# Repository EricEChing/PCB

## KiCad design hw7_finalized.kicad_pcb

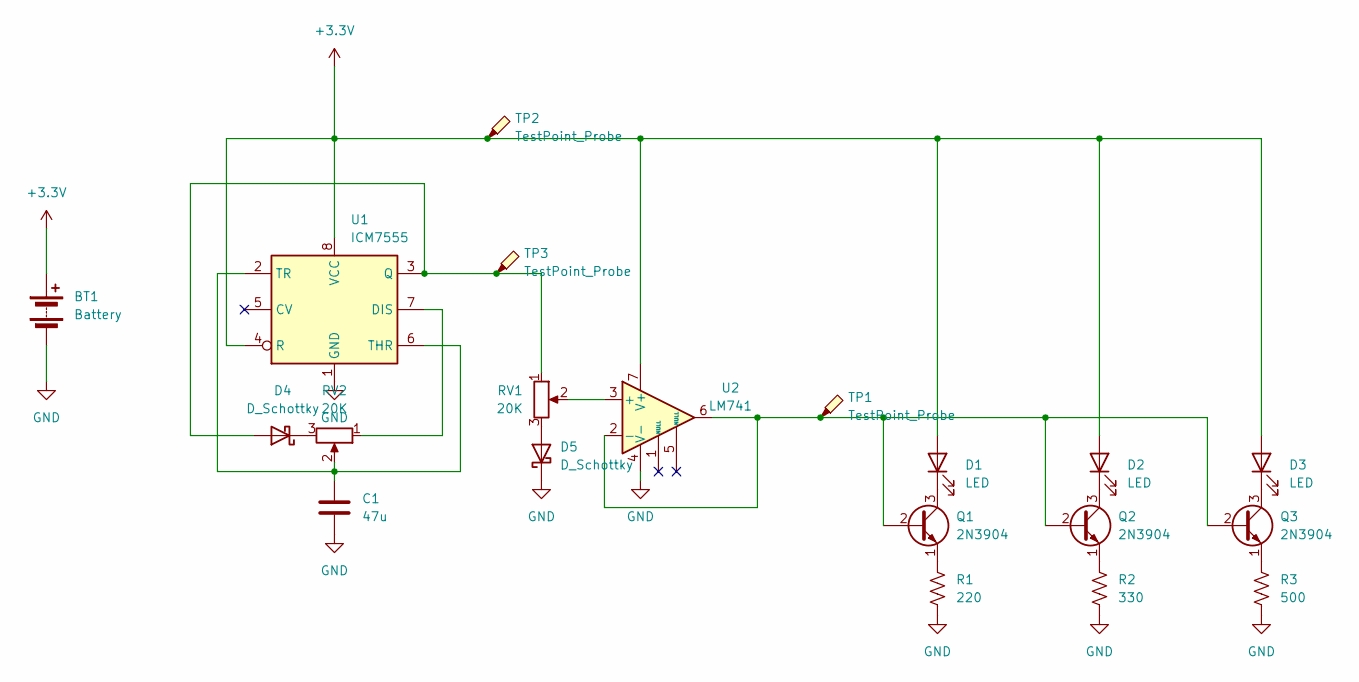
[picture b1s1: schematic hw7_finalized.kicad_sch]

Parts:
BT1: Battery; BAT_1026
C1: 47u; CP_Radial_D5.0mm_P2.00mm
D1, D2, D3: LED; LED_D3.0mm
D4, D5: D_Schottky; D_5KPW_P7.62mm_Vertical_AnodeUp
Q1, Q2, Q3: 2N3904; TO-92_Inline
R1: 220; R_Axial_DIN0207_L6.3mm_D2.5mm_P2.54mm_Vertical
R2: 330; R_Axial_DIN0207_L6.3mm_D2.5mm_P2.54mm_Vertical
R3: 500; R_Axial_DIN0207_L6.3mm_D2.5mm_P2.54mm_Vertical
RV1, RV2: 20K; Potentiometer_ACP_CA6-H2,5_Horizontal
TP1, TP2, TP3: TestPoint_Probe; TestPoint_Pad_D4.0mm
U1: ICM7555; DIP-8_W7.62mm
U2: LM741; DIP-8_W7.62mm

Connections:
+3.3V: BT1.P (+), D1.2 (A), D2.2 (A), D3.2 (A), TP2.1, U1.4 (R), U1.8 (VCC), U2.7 (V+)
GND: BT1.N (-), C1.2, D5.1 (K), R1.2, R2.2, R3.2, U1.1 (GND), U2.4 (V-)
unnamed: D1.1 (K), Q1.3 (C)
unnamed: D2.1 (K), Q2.3 (C)
unnamed: D3.1 (K), Q3.3 (C)
unnamed: D4.2 (A), RV1.1, TP3.1, U1.3 (Q)
unnamed: D4.1 (K), RV2.3
unnamed: D5.2 (A), RV1.3
unnamed: Q1.2 (B), Q2.2 (B), Q3.2 (B), TP1.1, U2.2 (-), U2.6
unnamed: Q1.1 (E), R1.1
unnamed: Q2.1 (E), R2.1
unnamed: Q3.1 (E), R3.1
unnamed: RV2.1, U1.7 (DIS)
unnamed: C1.1, RV2.2, U1.2 (TR), U1.6 (THR)
unnamed: RV1.2, U2.3 (+)

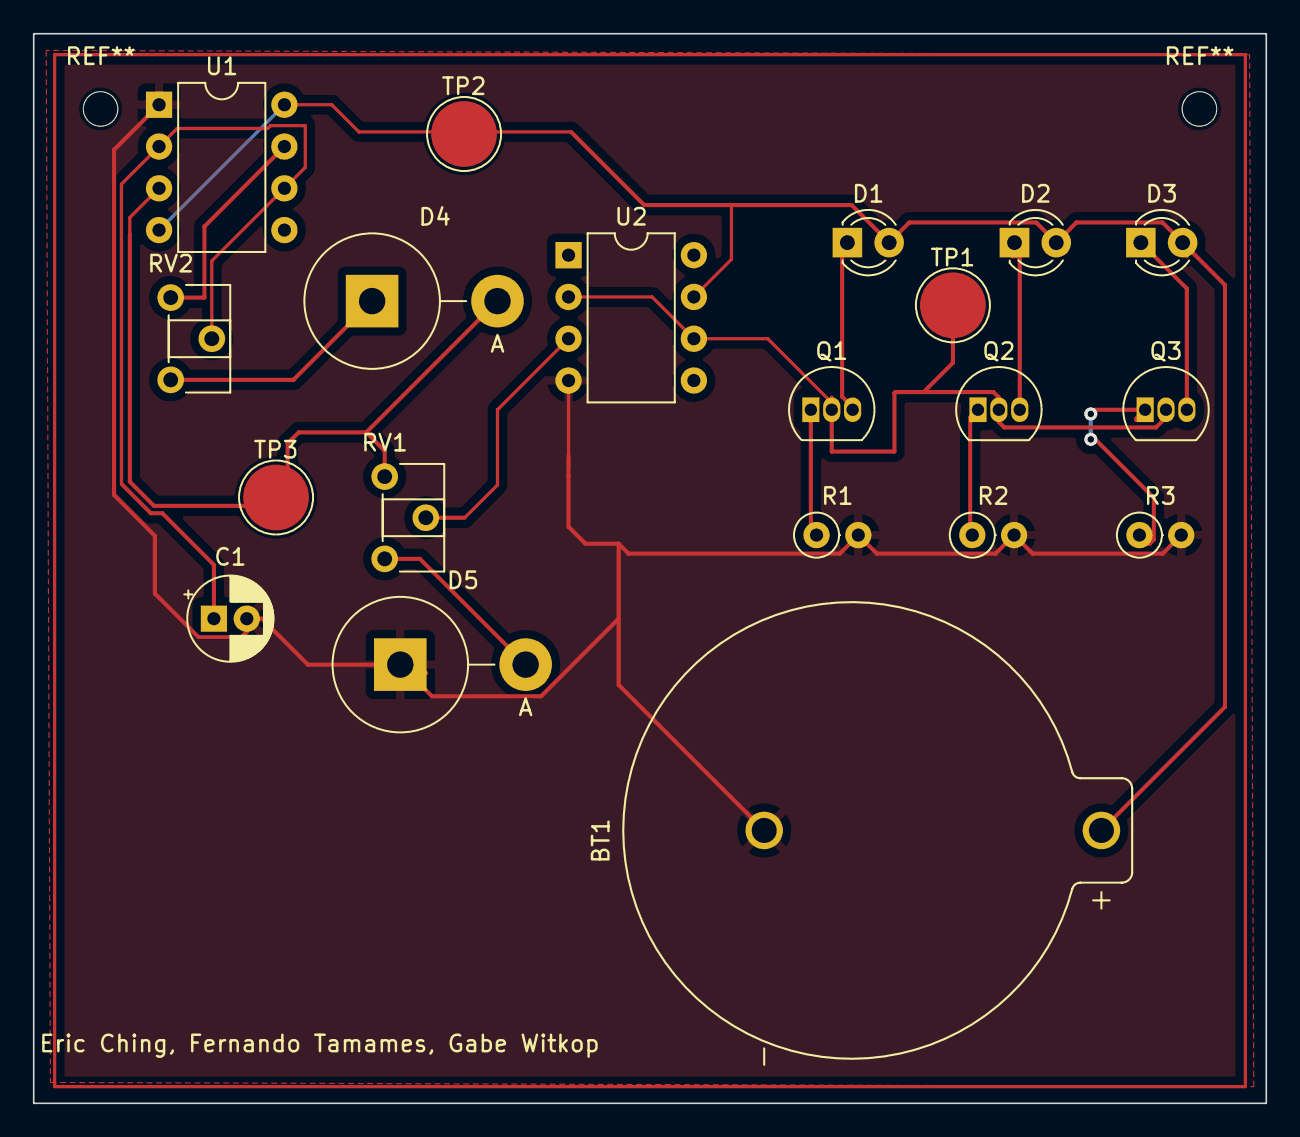
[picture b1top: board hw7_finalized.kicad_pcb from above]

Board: 2 copper layers, 74.9 x 65.0 mm, 20 parts (0 on the bottom side), 15 nets.

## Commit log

2023-11-23 File upload
    Hopefully I'm not forgetting anything.
